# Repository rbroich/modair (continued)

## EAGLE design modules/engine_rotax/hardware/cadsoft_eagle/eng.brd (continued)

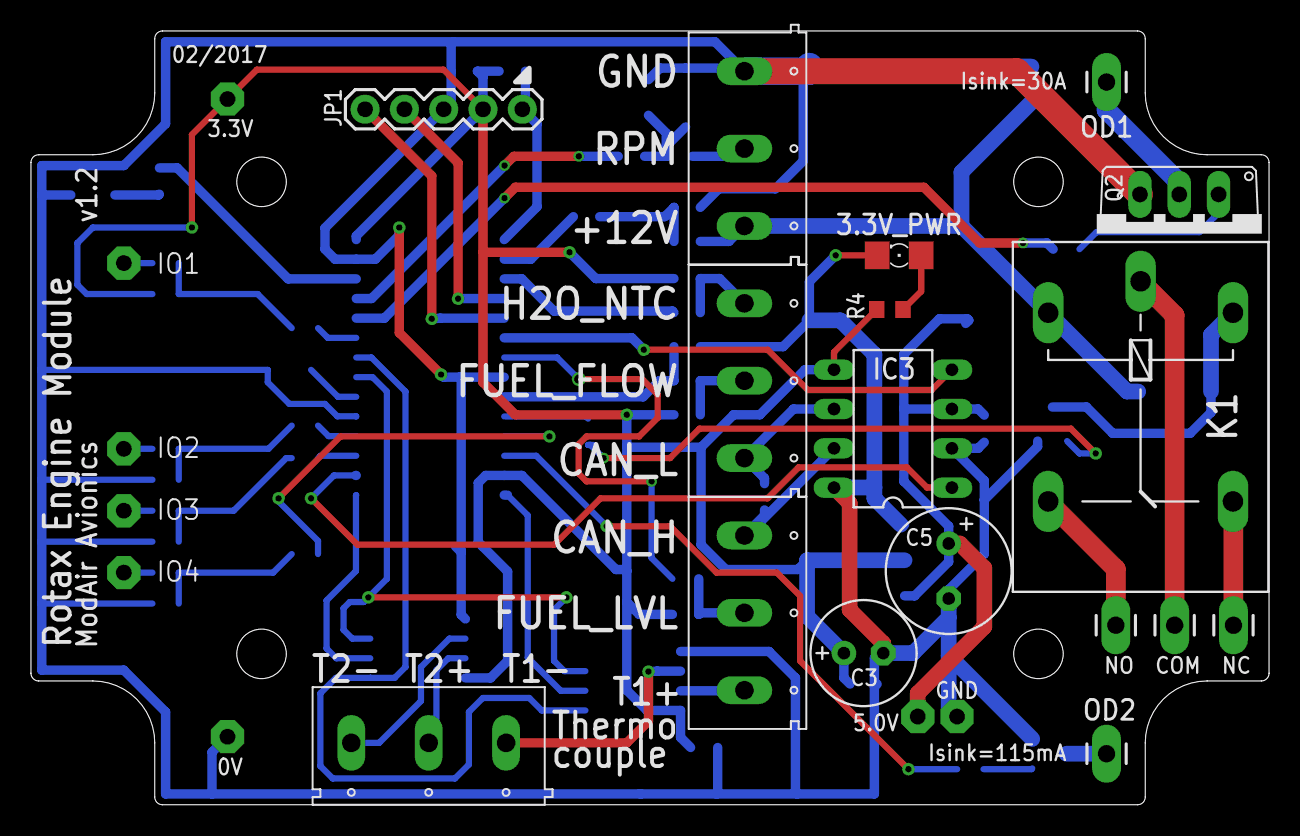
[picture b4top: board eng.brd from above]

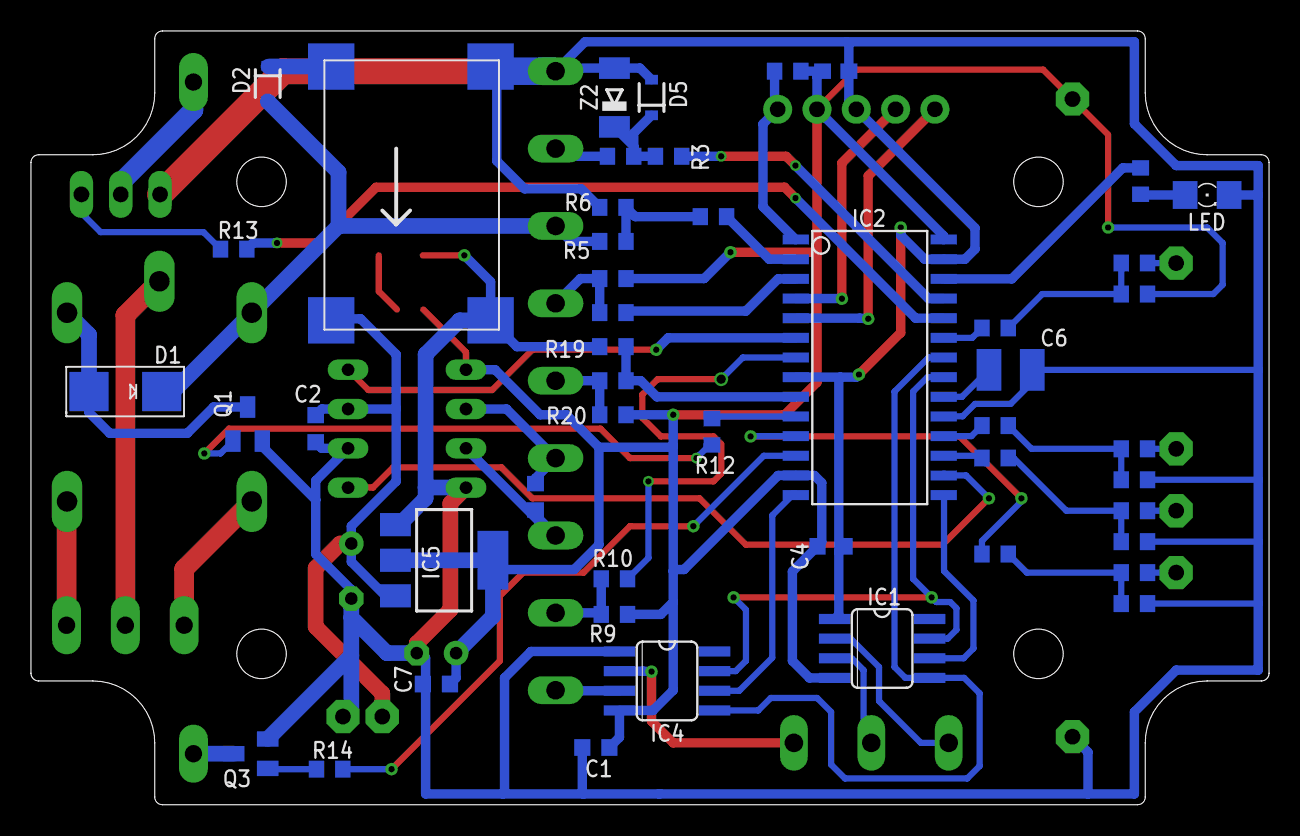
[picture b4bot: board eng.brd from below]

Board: 2 copper layers, 80.0 x 50.0 mm, 73 parts (48 on the bottom side), 59 nets.

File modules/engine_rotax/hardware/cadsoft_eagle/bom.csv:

"Qty";"Value";"Device";"Package";"Parts";"Description";"MF";"MPN";"OC_FARNELL";"OC_NEWARK";"PROD_ID";"VALUE";
"1";"";"DIODESMA";"SMADIODE";"D1";"Diode";"";"";"";"";"";"";
"2";"";"LED-FKIT-1206";"FKIT-LED-1206";"3.3V_PWR, LED";"LEDs";"";"";"";"";"";"";
"5";"";"M01PTH_LONGPAD";"1X01_LONGPAD";"COM, NC, NO, OD1, OD2";"Header 1";"";"";"";"";"";"";
"1";"";"M05PTH";"1X05";"JP1";"Header 5";"";"";"";"";"";"";
"1";"";"MOSFET-NREFLOW";"SOT23";"Q1";"N-Channel Mosfet";"";"";"";"";"";"";
"1";"1000u";"CPOL-EUE3.5-8";"E3,5-8";"C5";"POLARIZED CAPACITOR, European symbol";"";"";"";"";"";"";
"1";"100k";"R-EU_R0603";"R0603";"R18";"RESISTOR, European symbol";"";"";"";"";"";"";
"2";"100n";"C-EUC0603K";"C0603K";"C4, C7";"CAPACITOR, European symbol";"";"";"";"";"";"";
"1";"100u";"CPOL-EUE2.5-7";"E2,5-7";"C3";"POLARIZED CAPACITOR, European symbol";"";"";"";"";"";"";
"1";"10k";"R-EU_R0603";"R0603";"R11";"RESISTOR, European symbol";"";"";"";"";"";"";
"1";"10u";"C-EUC3225";"C3225";"C6";"CAPACITOR, European symbol";"";"";"";"";"";"";
"2";"120";"R-EU_R0603";"R0603";"R9, R21";"RESISTOR, European symbol";"";"";"";"";"";"";
"2";"150";"R-EU_R0603";"R0603";"R1, R4";"RESISTOR, European symbol";"";"";"";"";"";"";
"8";"1k";"R-EU_R0603";"R0603";"R3, R7, R8, R10, R12, R13, R14, R17";"RESISTOR, European symbol";"";"";"";"";"";"";
"1";"1k5";"R-EU_R0603";"R0603";"R6";"RESISTOR, European symbol";"";"";"";"";"";"";
"1";"1u";"C-EUC0603";"C0603";"C9";"CAPACITOR, European symbol";"";"";"";"";"";"";
"2";"1u";"C-EUC0603K";"C0603K";"C1, C2";"CAPACITOR, European symbol";"";"";"";"";"";"";
"1";"200k";"R-EU_R0603";"R0603";"R19";"RESISTOR, European symbol";"";"";"";"";"";"";
"2";"22k";"R-EU_R0603";"R0603";"R2, R5";"RESISTOR, European symbol";"";"";"";"";"";"";
"1";"2n7002";"MOSFET-NREFLOW";"SOT23";"Q3";"N-Channel Mosfet";"";"";"";"";"";"";
"1";"AMS1117-3.3";"LD117AS33TR";"SOT223";"IC5";"Low drop fixed and adjustable positive voltage regulators 1 A";"";"";"";"";"";"";
"1";"DSPIC33EP32GP502-I/SO";"DSPIC33EP32GP502-I/SO";"SO28W";"IC2";"16-Bit Microcontrollers and Digital Signal Controllers";"";"";"";"";"";"";
"1";"IRF540N";"MOSFET-NGDS_TO220V";"TO220V";"Q2";"N-Channel Mosfet";"";"";"";"";"";"";
"1";"JQC-3FF-12";"G5L";"G5LE";"K1";"RELAY";"";"";"unknown";"unknown";"";"";
"8";"LSP10";"LSP10";"LSP10";"0V, 3.3V, 5.0V, GND, IO1, IO2, IO3, IO4";"SOLDER PAD drill 1.0 mm, distributor Buerklin, 12H555";"";"";"";"";"";"";
"2";"MAX6675";"MAX6675";"SO08";"IC1, IC4";"Cold-Junction-Compensated K-Thermocouple-to-Digital Converter";"";"";"";"";"";"";
"1";"MCP2562-E/P";"MCP2562-E/P";"DIL8";"IC3";"High-Speed CAN Transceiver";"";"";"";"";"";"";
"1";"MINI_DC_DC_CONVSMD";"MINI_DC_DC_CONVSMD";"DSN-MINI-360-SMD";"U$1";"RC Airplane Module Mini 360 DC Buck Converter Step Down Module 4.75V-23V to 1V-17V 17x11x3.8mm New LM2596;";"";"";"";"";"";"";
"13";"N/A";"R-EU_R0603";"R0603";"R15, R16, R20, R23, R24, R25, R26, R29, R30, R31, R32, R35, R36";"RESISTOR, European symbol";"";"";"";"";"";"";
"2";"PMEG4005EJ";"DIODE-SCHOTTKY-PMEG4005EJ";"SOD-323";"D2, D5";"Schottky diodes in SFE's production catalog";"";"";"";"";"DIO-10955";"PMEG4005EJ";
"4";"XY301V-A";"XY301V-A";"XY301V-A";"CN1, CN2, CN3, CN4";"3 Pin Screw Terminal Block Connector 5mm Pitch 5.08-301-3P 301-3P 3pin";"";"";"";"";"";"";
"1";"Zener 3.3V";"DIODE-ZENERMM";"MINIMELF";"Z2";"Zener Diode";"";"";"";"";"";"";

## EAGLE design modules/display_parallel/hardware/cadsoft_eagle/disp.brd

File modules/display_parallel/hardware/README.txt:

Different Configurations:

Option 1: 5.8" WITSCHI_ERM25664AAG-1 EastRising 256x64 pixel graphic LCD module Blue backlight.
-LCD goes on top of PCB
-Headers row on the left aligns
-Mounting holes on the left align
-Top right mounting hole aligns with frame ground pad on LCD (solder spacer?)
-Electrolytic Caps C4 and C5 can be bent over
-Contrast Potentiometer not needed (already on LCD module)
-Rot Encoder header attached to Bottom
-LED (or header?) soldered on Bottom
-Screw Terminals attached to Bottom

Option 2: 2.9" NelyTech NT-G128641A 128x64 Graphic LCD Display Module 2xKS0108 Black on White.
-LCD goes on top of PCB
-Headers row on the bottom aligns
-All mounting holes align
-Bend electrolytic caps C4 and C5 over
-Contrast Potentiometer soldered
-Rot Encoder header attached to Bottom
-LED (or header?) soldered on Bottom
-Screw Terminals attached to Bottom

Option 3: 3.1" Generic 5V 12864B V2.0 LCD Display Module 128x64 Dots Graphic Matrix LCD Blue Backlight
-Identical mounting to Option 2
-CS1 becomes PSB [parallel mode] (ST7920, 2MHz clock rate)
-CS2 is not used
-Contrast Potentiometer not needed (already on LCD module)
-Backlight Resistor already on LCD module. Drive with 5V

Option 4: Generic HD44780 2x16 Character LCD Blue Backlight
-Cut PCB Smaller
-LCD goes on top of PCB, rotated 180 degrees
-Headers row on the bottom right aligns
-All mounting holes align
-Rot Encoder mounts vertically on top left PCB (isolate exposed header pins underneath...gnd plate on bottom of rotenc)
-LED mounts vertically on top right
-Electrolytic caps C4 and C5 mount vertically
-Screw Terminals attached to Bottom

ASSEMBLY:
Option 2 & 3:
-3D printed mounting hole standoffs with outer rectangle
-11mm Standoffs (distance between LCD and PCB)
-Male headers on LCD
-Female headers on PCB
-1.6mm PCBs

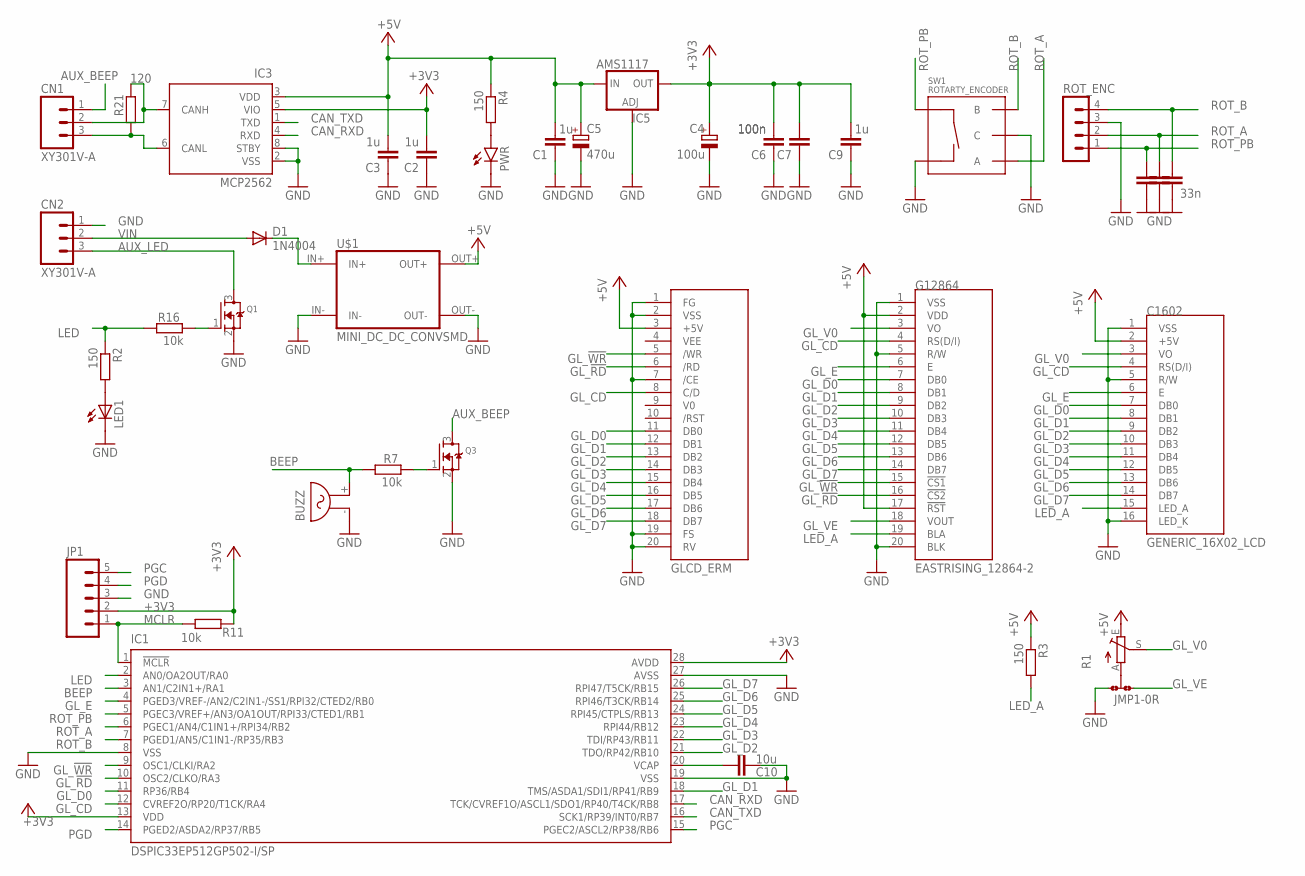
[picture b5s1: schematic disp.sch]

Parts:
BUZZ: F/QMX
C1, C2, C3, C9: 1u; C0603K
C4: 100u; E2,5-7
C5: 470u; E3,5-8
C6, C7: 100n; C0603K
C10: 10u; C025-030X050
C11, C12, C13: 33n; C0603K
C1602: GENERIC_16X02_LCD; 1X16
CN1, CN2: XY301V-A
D1: 1N4004; DO41-10
G12864: EASTRISING_12864-2; 1X20
GLCD_ERM: WITSCHI_ERM25664AAG-1; 1X20
IC1: DSPIC33EP512GP502-I/SP; DIL28-3
IC3: MCP2562; DIL8
IC5: AMS1117; SOT223
JMP1: 0R-JUMPB; B0R-JMP
JP1: M05PTH; 1X05
LED1: LED5MM
PWR: LED-FKIT-1206; FKIT-LED-1206
Q1, Q3: MOSFET-NREFLOW; SOT23
R1: TRIM_EU-B64Y; B64Y
R2, R3, R4: 150; R0603
R7, R11, R16: 10k; R0603
R21: 120; R0603
ROT_ENC: MA04-1
SW1: ROTARTY_ENCODER; ROTARY_ENC_PLAIN
U$1: MINI_DC_DC_CONVSMD; DSN-MINI-360-SMD

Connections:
+3V3: C2.2, C4.+, C6.2, C7.2, C9.2, IC1.13 (VDD), IC1.28 (AVDD), IC3.5 (VIO), IC5.2 (OUT), IC5.@2 (OUT), JP1.2, R11.1
+5V: C1.2, C3.2, C5.+, C1602.2 (+5V), G12864.2 (VDD), G12864.17 (!RST), GLCD_ERM.3 (+5V), IC3.3 (VDD), IC5.3 (IN), R1.E, R3.1, R4.1, U$1.OUT+
AUX_BEEP: CN1.1, Q3.3 (D)
AUX_LED: CN2.3, Q1.3 (D)
BEEP: BUZZ.+ (2), IC1.3 (AN1/C2IN1+/RA1), R7.2
CAN_H: CN1.2, IC3.7 (CANH), R21.2
CAN_L: CN1.3, IC3.6 (CANL), R21.1
CAN_RXD: IC1.17 (TCK/CVREF1O/ASCL1/SDO1/RP40/T4CK/RB8), IC3.4 (RXD)
CAN_TXD: IC1.16 (SCK1/RP39/INT0/RB7), IC3.1 (TXD)
GL_!RD: G12864.16 (!CS2), GLCD_ERM.6 (/RD), IC1.10 (OSC2/CLKO/RA3)
GL_!WR: G12864.15 (!CS1), GLCD_ERM.5 (/WR), IC1.9 (OSC1/CLKI/RA2)
GL_CD: C1602.4 (RS(D/I)), G12864.4 (RS(D/I)), GLCD_ERM.8 (C/D), IC1.12 (CVREF2O/RP20/T1CK/RA4)
GL_D0: C1602.7 (DB0), G12864.7 (DB0), GLCD_ERM.11 (DB0), IC1.11 (RP36/RB4)
GL_D1: C1602.8 (DB1), G12864.8 (DB1), GLCD_ERM.12 (DB1), IC1.18 (TMS/ASDA1/SDI1/RP41/RB9)
GL_D2: C1602.9 (DB2), G12864.9 (DB2), GLCD_ERM.13 (DB2), IC1.21 (TDO/RP42/RB10)
GL_D3: C1602.10 (DB3), G12864.10 (DB3), GLCD_ERM.14 (DB3), IC1.22 (TDI/RP43/RB11)
GL_D4: C1602.11 (DB4), G12864.11 (DB4), GLCD_ERM.15 (DB4), IC1.23 (RPI44/RB12)
GL_D5: C1602.12 (DB5), G12864.12 (DB5), GLCD_ERM.16 (DB5), IC1.24 (RPI45/CTPLS/RB13)
GL_D6: C1602.13 (DB6), G12864.13 (DB6), GLCD_ERM.17 (DB6), IC1.25 (RPI46/T3CK/RB14)
GL_D7: C1602.14 (DB7), G12864.14 (DB7), GLCD_ERM.18 (DB7), IC1.26 (RPI47/T5CK/RB15)
GL_E: C1602.6 (E), G12864.6 (E), IC1.4 (PGED3/VREF-/AN2/C2IN1-/SS1/RPI32/CTED2/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)
GL_V0: C1602.3 (VO), G12864.3 (VO), R1.S
GL_VE: G12864.18 (VOUT), JMP1.3
GND: BUZZ.- (1), C1.1, C2.1, C3.1, C4.-, C5.-, C6.1, C7.1, C9.1, C10.1, C11.1, C12.1, C13.1, C1602.1 (VSS), C1602.5 (R/W), C1602.16 (LED_K), CN2.1, G12864.1 (VSS), G12864.5 (R/W), G12864.20 (BLK), GLCD_ERM.1 (FG), GLCD_ERM.2 (VSS), GLCD_ERM.7 (/CE), GLCD_ERM.19 (FS), GLCD_ERM.20 (RV), IC1.8 (VSS), IC1.19 (VSS), IC1.27 (AVSS), IC3.2 (VSS), IC3.8 (STBY), IC5.1 (ADJ), JMP1.1, JP1.3, LED1.K (C), PWR.C, Q1.2 (S), Q3.2 (S), ROT_ENC.3, SW1.C, SW1.SW-, U$1.IN-, U$1.OUT-
LED: IC1.2 (AN0/OA2OUT/RA0), R2.1, R16.2
LED_A: C1602.15 (LED_A), G12864.19 (BLA), R3.2
MCLR: IC1.1 (!MCLR!), JP1.1, R11.2
unnamed: Q3.1 (G), R7.1
unnamed: LED1.A, R2.2
unnamed: PWR.A, R4.2
unnamed: JMP1.2, R1.A
unnamed: Q1.1 (G), R16.1
PGC: IC1.15 (PGEC2/ASCL2/RP38/RB6), JP1.5
PGD: IC1.14 (PGED2/ASDA2/RP37/RB5), JP1.4
ROT_A: C12.2, IC1.6 (PGEC1/AN4/C1IN1+/RPI34/RB2), ROT_ENC.2, SW1.A
ROT_B: C13.2, IC1.7 (PGED1/AN5/C1IN1-/RP35/RB3), ROT_ENC.4, SW1.B
ROT_PB: C11.2, IC1.5 (PGEC3/VREF+/AN3/OA1OUT/RPI33/CTED1/RB1), ROT_ENC.1, SW1.SW+
V0: GLCD_ERM.9 (V0)
VCAP: C10.2, IC1.20 (VCAP)
VEE: GLCD_ERM.4 (VEE)
VIN: CN2.2, D1.A
VIN_D: D1.C, U$1.IN+

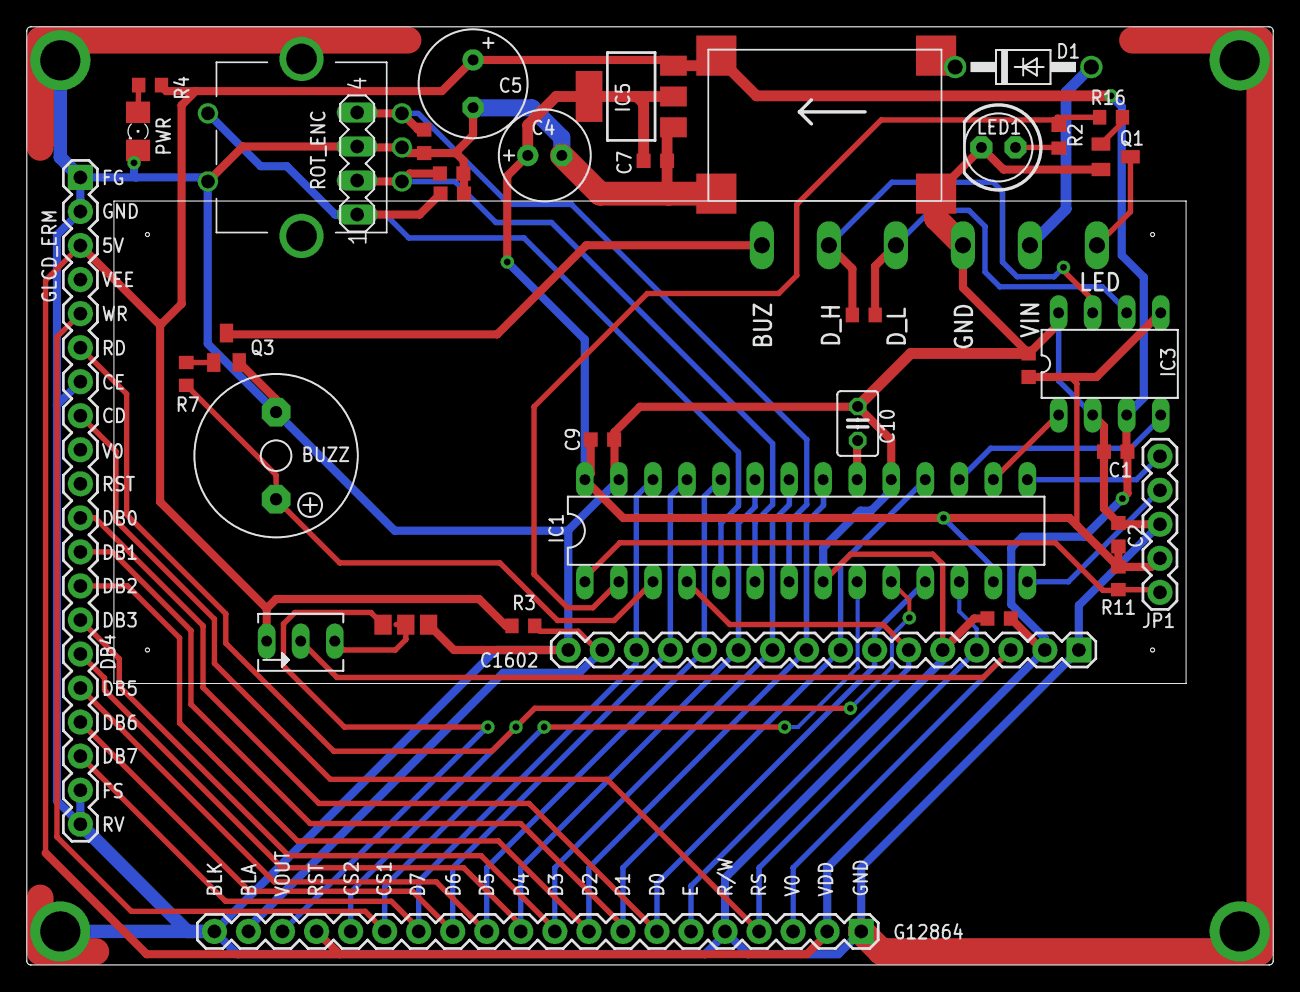
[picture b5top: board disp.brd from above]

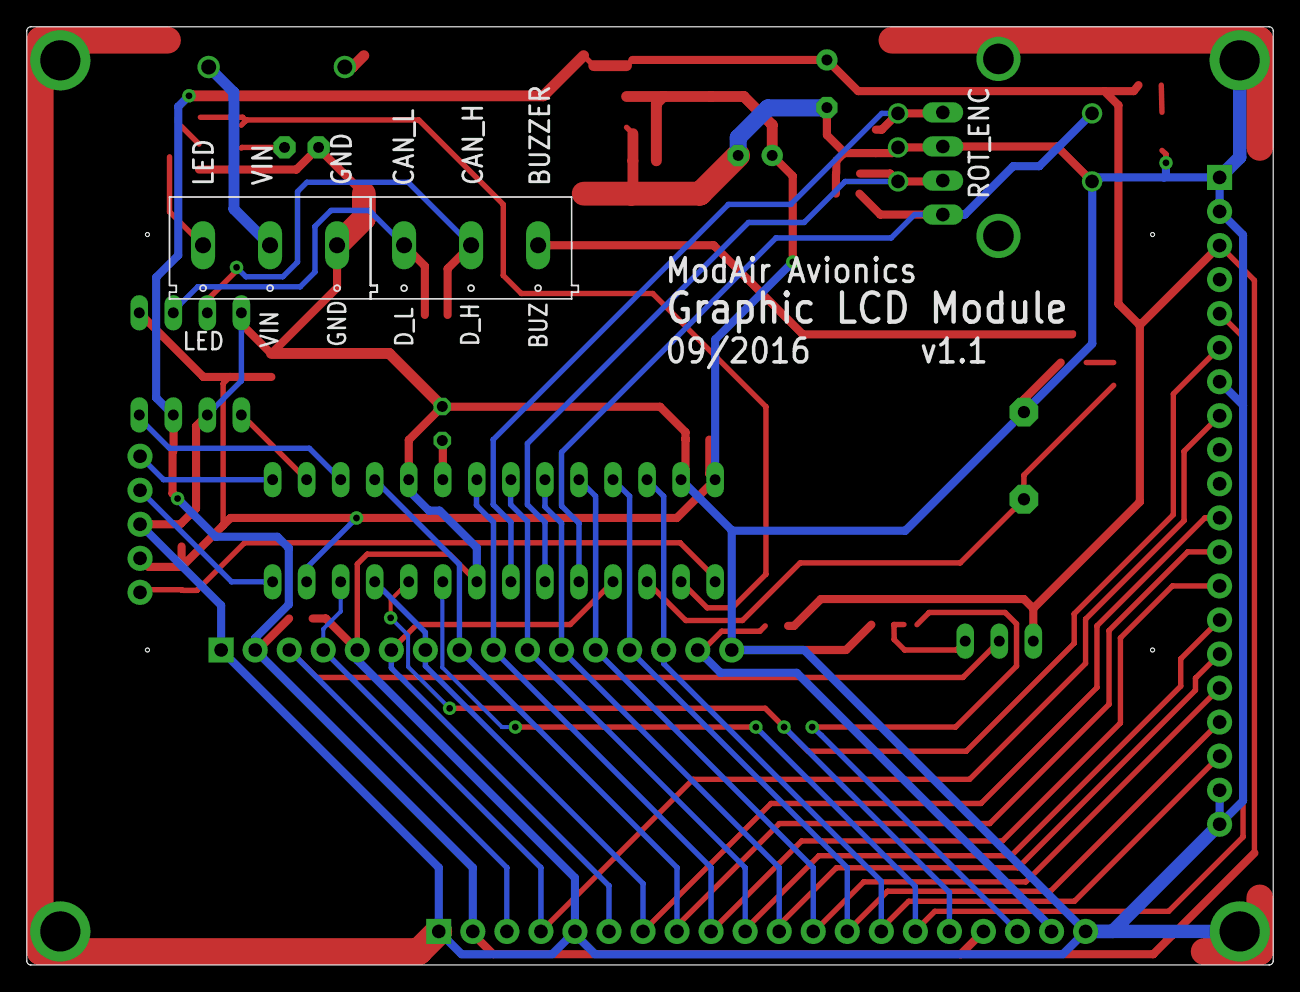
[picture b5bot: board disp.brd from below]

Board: 2 copper layers, 93.0 x 70.0 mm, 39 parts (2 on the bottom side), 40 nets.

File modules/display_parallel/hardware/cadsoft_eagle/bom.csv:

"Qty";"Value";"Device";"Package";"Parts";"Description";"MF";"MPN";"OC_FARNELL";"OC_NEWARK";
"1";"";"LED-FKIT-1206";"FKIT-LED-1206";"PWR";"LEDs";"";"";"";"";
"1";"";"LED5MM";"LED5MM";"LED1";"LED";"";"";"";"";
"1";"";"M05PTH";"1X05";"JP1";"Header 5";"";"";"";"";
"1";"";"MA04-1";"MA04-1";"ROT_ENC";"PIN HEADER";"";"";"unknown";"unknown";
"2";"";"MOSFET-NREFLOW";"SOT23";"Q1, Q3";"N-Channel Mosfet";"";"";"";"";
"1";"";"TRIM_EU-B64Y";"B64Y";"R1";"POTENTIOMETER";"";"";"";"";
"1";"0R-JUMPB";"0R-JUMPB";"B0R-JMP";"JMP1";"SMD 0R 0805 Jumper";"";"";"";"";
"2";"100n";"C-EUC0603K";"C0603K";"C6, C7";"CAPACITOR, European symbol";"";"";"";"";
"1";"100u";"CPOL-EUE2.5-7";"E2,5-7";"C4";"POLARIZED CAPACITOR, European symbol";"";"";"";"";
"3";"10k";"R-EU_R0603";"R0603";"R7, R11, R16";"RESISTOR, European symbol";"";"";"";"";
"1";"10u";"C-EU025-030X050";"C025-030X050";"C10";"CAPACITOR, European symbol";"";"";"";"";
"1";"120";"R-EU_R0603";"R0603";"R21";"RESISTOR, European symbol";"";"";"";"";
"3";"150";"R-EU_R0603";"R0603";"R2, R3, R4";"RESISTOR, European symbol";"";"";"";"";
"1";"1N4004";"1N4004";"DO41-10";"D1";"DIODE";"";"";"";"";
"4";"1u";"C-EUC0603K";"C0603K";"C1, C2, C3, C9";"CAPACITOR, European symbol";"";"";"";"";
"3";"33n";"C-EUC0603K";"C0603K";"C11, C12, C13";"CAPACITOR, European symbol";"";"";"";"";
"1";"470u";"CPOL-EUE3.5-8";"E3,5-8";"C5";"POLARIZED CAPACITOR, European symbol";"";"";"";"";
"1";"AMS1117";"LD117AS33TR";"SOT223";"IC5";"Low drop fixed and adjustable positive voltage regulators 1 A";"";"";"";"";
"1";"DSPIC33EP512GP502-I/SP";"DSPIC33EP512GP502-I/SP";"DIL28-3";"IC1";"16-Bit Microcontrollers and Digital Signal Controllers";"";"";"";"";
"1";"EASTRISING_12864-2";"EASTRISING_12864-2";"1X20";"G12864";"2.9"128x64 Graphic LCD Display Module KS0108 Black on White.";"";"";"";"";
"1";"F/QMX";"F/QMX";"F/QMX";"BUZZ";"BUZZER Source: Buerklin";"";"";"unknown";"unknown";
"1";"GENERIC_16X02_LCD";"GENERIC_16X02_LCD";"1X16";"C1602";"";"";"";"";"";
"1";"MCP2562";"MCP2562-E/P";"DIL8";"IC3";"High-Speed CAN Transceiver";"";"";"";"";
"1";"MINI_DC_DC_CONVSMD";"MINI_DC_DC_CONVSMD";"DSN-MINI-360-SMD";"U$1";"RC Airplane Module Mini 360 DC Buck Converter Step Down Module 4.75V-23V to 1V-17V 17x11x3.8mm New LM2596;";"";"";"";"";
"1";"ROTARTY_ENCODER";"ROTARTY_ENCODER";"ROTARY_ENC_PLAIN";"SW1";"Simple no LED rotary encoder";"";"";"";"";
"1";"WITSCHI_ERM25664AAG-1";"WITSCHI_ERM25664AAG-1";"1X20";"GLCD_ERM";"EastRising 256x64 pixel graphic LCD module";"";"";"";"";
"2";"XY301V-A";"XY301V-A";"XY301V-A";"CN1, CN2";"3 Pin Screw Terminal Block Connector 5mm Pitch 5.08-301-3P 301-3P 3pin";"";"";"";"";

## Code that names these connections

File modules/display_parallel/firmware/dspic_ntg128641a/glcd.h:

#ifndef GLCD_H
#define GLCD_H

// 2.9" NelyTech NT-G128641A 128x64 Graphic LCD Display Module, Black on White
// PCB 93x70 mm
// 2 x KS0108 Controllers

// All minimum timing requirements multiplied by 2 (fosc 270kHz instead of 540kHz)

// Pin 01 VSS
// Pin 02 VDD
// Pin 03 V0
// Pin 04 RS (RS=H:data  RS=L:instruction)
// Pin 05 R/W (RW=H:read  RW=L:write)
// Pin 06 E
// Pin 07 DB0
// Pin ......
// Pin 14 DB7
// Pin 15 CS1
// Pin 16 CS2
// Pin 17 /RST
// Pin 18 VOUT
// Pin 19 LED A (+)
// Pin 20 LED K (-)

// Standard graphical axis
// x=0: left
// x=LCD_X-1: right
// y=0: top
// y=LCD_Y-1: bottom

#include "common.h"

#define ROTATE_SCREEN_90        1
#if ROTATE_SCREEN_90
  #define LCD_X                   64
  #define LCD_Y                   128
#else
  #define LCD_X                   128
  #define LCD_Y                   64
#endif
#define LCD_WHITE               0
#define LCD_BLACK               1

#define GL_RS_INSTR             0
#define GL_RS_DATA              1

#define GL_RS                   _LATA4 // GL_CD
#define GL_E                    _LATB0
#define GL_D0                   _LATB4
#define GL_D1                   _LATB9
#define GL_D2                   _LATB10
#define GL_D3                   _LATB11
#define GL_D4                   _LATB12
#define GL_D5                   _LATB13
#define GL_D6                   _LATB14
#define GL_D7                   _LATB15
#define GL_CS1                  _LATA2 // GL_CS1 == GL_!WR
#define GL_CS2                  _LATA3 // GL_CS2 == GL_!RD

#define LCD_SET_ADDR            0x40
#define LCD_SET_PAGE            0xB8
#define LCD_START_LINE          0xC0
#define LCD_OFF                 0x3E
#define LCD_ON                  0x3F

#define lcd_ctrl_out()  (TRISA &= 0b1111111111100011)
#define lcd_dir_out()   (TRISB &= 0b0000000111101110)
#define lcd_data_out(x) (LATB = (LATB&0b111101111) | ((x&0xFE)<<8) | ((x&0x01)<<4))



void lcd_out(u8 val);
void lcd_cmd(u8 val);
void lcd_init(void);
void lcd_fill(u8 color);
void lcd_update(void);
void lcd_clrbuff(void);
void lcd_setpixel(u8 x, u8 y, u8 color);

#endif

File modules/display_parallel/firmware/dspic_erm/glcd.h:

#ifndef GLCD_H
#define GLCD_H

#include "common.h"

#define LCD_Y           64
#define LCD_X           256
#define LCD_WHITE       0
#define LCD_BLACK       1

#define LCD_CHAR_WIDTH  8 // 6 or 8 bits depending on FS (H:6x8 L:8x8)

#define LCD_D7          _RB15
#define LCD_D6          _RB14
#define LCD_D5          _RB13
#define LCD_D4          _RB12
#define LCD_D3          _RB11
#define LCD_D2          _RB10
#define LCD_D1          _RB9
#define LCD_D0          _RB4
#define LCD_nWE         _LATA2
#define LCD_nRE         _LATA3
#define LCD_CD          _LATA4

#define lcd_out(x)      (LATB = (LATB&0b111101111) | ((x&0xFE)<<8) | ((x&0x01)<<4))
#define lcd_in(x)       (x = ((PORTB&0xFE00) >> 8) | ((PORTB&0x0010)>>4))
#define lcd_dir_in()    (TRISB |= 0b1111111000010000)
#define lcd_dir_out()   (TRISB &= 0b0000000111101111)
#define lcd_ctrl_out()  (TRISA &= 0b1111111111100011)
#define lcd_cd_cmd()    (LCD_CD=1)
#define lcd_cd_data()   (LCD_CD=0)
#define lcd_rw_idle()   {LCD_nWE=1;LCD_nRE=1;}
#define lcd_rw_rd()     {LCD_nWE=1;LCD_nRE=0;}
#define lcd_rw_wr()     {LCD_nWE=0;LCD_nRE=1;}

/* Define the Memory Map */
#define LCD_GRAPHICS_HOME   0x0000  /* This will usually be at the start of RAM */
#define LCD_GRAPHICS_AREA   0x14    /* A graphic character is 8 bits wide (same as 8x8 char) */
#define LCD_GRAPHICS_SIZE   0x0800  /* Size of graphics RAM */
#define LCD_TEXT_HOME       0x0A00  /* Graphics Area + Text Attribute Size (same size as text size) */
#define LCD_TEXT_AREA       0x14    /* Text line is 20 chars wide */
#define LCD_TEXT_SIZE       0x0200  /* Size of text RAM */

// Control Words
#define LCD_CURSOR_POINTER_SET          0b00100001
#define LCD_OFFSET_REGISTER_SET         0b00100010
#define LCD_ADDRESS_POINTER_SET         0b00100100
#define LCD_TEXT_HOME_ADDRESS_SET       0b01000000
#define LCD_TEXT_AREA_SET               0b01000001
#define LCD_GRAPHIC_HOME_ADDRESS_SET    0b01000010
#define LCD_GRAPHIC_AREA_SET            0b01000011

#define LCD_CG_ROM_MODE_OR              0b10000000
#define LCD_CG_ROM_MODE_EXOR            0b10000001
#define LCD_CG_ROM_MODE_AND             0b10000011
#define LCD_CG_ROM_MODE_TEXT            0b10000100
#define LCD_CG_RAM_MODE_OR              0b10001000
#define LCD_CG_RAM_MODE_EXOR            0b10001001
#define LCD_CG_RAM_MODE_AND             0b10001011
#define LCD_CG_RAM_MODE_TEXT            0b10001100

// OR together for ON modes
#define LCD_DISPLAY_MODES_ALL_OFF       0b10010000
#define LCD_DISPLAY_MODES_GRAPHICS_ON   0b10011000
#define LCD_DISPLAY_MODES_TEXT_ON       0b10010100
#define LCD_DISPLAY_MODES_CURSOR_ON     0b10010010
#define LCD_DISPLAY_MODES_CURSOR_BLINK  0b10010001

// Cursor Pattern Select
#define LCD_CURSOR_PATTERN_UNDERLINE    0b10100000
#define LCD_CURSOR_PATTERN_BLOCK        0b10100111

// Send Auto_XX Command, then block of data, then Auto_reset
#define LCD_DATA_AUTO_WRITE_SET         0b10110000
#define LCD_DATA_AUTO_READ_SET          0b10110001
#define LCD_DATA_AUTO_RESET             0b10110010

// Send R/W Then one byte Data
#define LCD_DATA_WRITE_AUTO_INCREMENT   0b11000000
#define LCD_DATA_READ_AUTO_INCREMENT    0b11000001
#define LCD_DATA_WRITE_NO_INCREMENT     0b11000100
#define LCD_DATA_READ_NO_INCREMENT      0b11000101

// Status Register Bits
#define LCD_STATUS_BUSY1    0x01
#define LCD_STATUS_BUSY2    0x02
#define LCD_STATUS_DARRDY   0x04
#define LCD_STATUS_DAWRDY   0x08
#define LCD_STATUS_CLR      0x20
#define LCD_STATUS_ERR      0x40
#define LCD_STATUS_BLINK    0x80

void lcd_write_command(u8 cmd);
void lcd_write_data(u8 data);
u8 lcd_read_data(void);
u8 lcd_read_status(void);
void lcd_init(void);
void lcd_update(void);
void lcd_clrbuff(void);
void lcd_setpixel(u8 x, u8 y, u8 color);

#endif

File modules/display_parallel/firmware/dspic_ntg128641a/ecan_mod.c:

#include "ecan_mod.h"

__attribute__((aligned(NR_ECAN_BUF*16))) u16 ecan_buf[NR_ECAN_BUF][8];

extern void ecan_rx(u16 pid, u16 *data, u8 msg_type, u8 flags, u8 len);

void ecan_irq(void)
{
    u8 buf_sel = C1VECbits.ICODE;
    if (!(ecan_buf[buf_sel][0] & 0x0001)) // Extended Identifier (29-bit ID)
        return;

    // CID = CAN-ID = 0b000s.ssss.ssss.ssee.eeee.eeee.eeee.eeee
    // where s [bit28:18] = SID (11 bit)
    //       e [bit17:00] = EID (18 bit)
    u8 msg_type = (ecan_buf[buf_sel][0] & 0x0FF0) >> 4;
    u8 len = ecan_buf[buf_sel][2]&0x000F; // Data Length Code
    u16 pid = ecan_buf[buf_sel][2] >> 10;
    pid |= ecan_buf[buf_sel][1] << 6;
    u8 flags = (ecan_buf[buf_sel][1] & 0x0C00) >> 10;
    if (ecan_buf[buf_sel][2] & 0x0200) // remote frame request
        flags |= ECAN_FLAGS_RTR;
    ecan_rx(pid, &ecan_buf[buf_sel][3], msg_type, flags, len);
    C1RXFUL1 = 0xFFFF ^ (1<<buf_sel); // Clear Rx Buffer Full Flag
    C1INTFbits.TBIF = 0; // Clear TX Buffer Interrupt Flag
    C1INTFbits.RBIF = 0; // Clear RX Buffer Interrupt Flag
}

void ecan_tx(u16 pid, u16 d0, u16 d2, u16 d4, u16 d6, u8 msg_type, u8 flags, u8 len)
{
    while (_TXREQ0) ; // wait for first transmit buffer to become available
    // Always transmit using Extended Identifier format
    ecan_buf[0][0] = (msg_type<<4) | 0b11;
    ecan_buf[0][1] = ((pid&0xFFC0)>>6) | ((flags&0x03)<<10);
    ecan_buf[0][2] = ((pid&0x003F)<<10) | ((flags&ECAN_FLAGS_RTR)?0x200:0) | len;
    ecan_buf[0][3] = d0; // byte 0 and 1
    ecan_buf[0][4] = d2; // byte 2 and 3
    ecan_buf[0][5] = d4; // byte 4 and 5
    ecan_buf[0][6] = d6; // byte 6 and 7
    _TXREQ0=1;
}

void ecan_init(void)
{
    // I/O Pin direction, mode, and re-mapping (PPS)
    U1RXt = INPUT_PIN;
    U1TX = 1; // recessive state by default
    U1TXt = OUTPUT_PIN;
    U1RXa = DIGITAL_PIN;
    _RP39R = 14; // CAN_TXD (output) RB7 == RP39 <- C1TX (TABLE 11-3 in DS70000657H)
    _C1RXR = 40; // CAN_RXD (input)  RB8 == RP40 -> C1RX (TABLE 11-2 in DS70000657H)

    C1CTRL1bits.REQOP = 0b100; // enter config mode
    while(C1CTRL1bits.OPMODE != 0b100); // wait for config mode

    // Memory Map Select (0 or 1: C1CTRLx,C1VEC,C1FCTRL,C1FIFO,C1INTF,C1INTE,C1EC,C1CFGx,C1FEN1,C1FMSKSELx)

    // Set Bit Timing to 1 Mbps
    // N = 20 time quanta per bit;   FTQ = N x baud = 20 MHz
    C1CTRL1bits.CANCKS = 1; // FCAN is equal to 2*FP (==2*F_CY)
    C1CFG2bits.SEG1PH = 0x7; // Phase Segment 1 time is 8 TQ
    C1CFG2bits.SEG2PHTS = 0x1; // Phase Segment 2 time is set to be programmable
    C1CFG2bits.SEG2PH = 0x5; // Phase Segment 2 time is 6 TQ
    C1CFG2bits.PRSEG = 0x4; // Propagation Segment time is 5 TQ
    C1CFG2bits.SAM = 0x1; // Bus line is sampled three times at the sample point
    C1CFG1bits.SJW = 0x3; // Synchronization Jump Width set to 4 TQ
    C1CFG1bits.BRP = 0x2; // Baud Rate Prescaler = FCAN /(2*FTQ) -1

    // Memory Map Select (1: C1BUFPNTx,C1RXMxSID,C1RXMxEID,C1RXFxSID,C1RXFxEID)
    C1CTRL1bits.WIN = 1;

    // Configure Receive Buffers [buffers 8 to 15]
    C1FCTRLbits.DMABS = 0b100; // 16 buffers in device RAM
    C1FCTRLbits.FSA = 8; // FIFO starts at buffer 8 (rx buffers)
    C1RXF0SIDbits.SID = 0; // configure filter 0
    C1RXF0SIDbits.EXIDE = 1; // extended identifier address
    C1RXF0SIDbits.EID = 0;
	C1RXF0EIDbits.EID = 0;
    C1BUFPNT1bits.F0BP = 0b1111; // assign filter 0 to FIFO
    C1RXM0SIDbits.SID = 0; // configure mask 0 (all bits are ignored in filter comparison)
    C1RXM0EIDbits.EID = 0;
    C1FMSKSEL1bits.F0MSK = 0; // select mask 0 for filter 0
	C1FEN1 = 0x1; // enable filter 0

    // Memory Map Select (0: C1RXFULx,C1RXOVFx,C1TRxxCON,C1RXD,C1TXD)
    C1CTRL1bits.WIN = 0;

    // Configure Transmit Buffers [buffers 0 to 7]
    C1TR01CONbits.TXEN0 = ENABLE; // buffers are transmit buffers
    C1TR01CONbits.TXEN1 = ENABLE;
    C1TR23CONbits.TXEN2 = ENABLE;
    C1TR23CONbits.TXEN3 = ENABLE;
    C1TR45CONbits.TXEN4 = ENABLE;
    C1TR45CONbits.TXEN5 = ENABLE;
    C1TR67CONbits.TXEN6 = ENABLE;
    C1TR67CONbits.TXEN7 = ENABLE;

    // Setup DMA0 for TX_RAM -> CAN_TX
    DMA0CONbits.SIZE = 0x0; // word instead of byte
    DMA0CONbits.DIR = 0x1; // read from RAM address, write to peripheral address
    DMA0CONbits.AMODE = 0x2; // Peripheral Indirect Addressing mode
    DMA0CONbits.MODE = 0x0; // Continuous, Ping-Pong modes disabled
    DMA0REQ = 70; // DMA Peripheral IRQ Number Select: ECAN1 ? TX Data Request
    DMA0CNT = 7;
    DMA0PAD = (volatile u16)&C1TXD;
    DMA0STAL = (u16)&ecan_buf[0][0];
    DMA0STAH = (u16)&ecan_buf[0][0];
    DMA0CONbits.CHEN = ENABLE;

    // Setup DMA1 for CAN_RX -> RX_RAM
    DMA1CONbits.SIZE = 0x0; // word instead of byte
    DMA1CONbits.DIR = 0x0; // Read from Peripheral address, write to RAM address
    DMA1CONbits.AMODE = 0x2; // Peripheral Indirect Addressing mode
    DMA1CONbits.MODE = 0x0; // Continuous, Ping-Pong modes disabled
    DMA1REQ = 34; // DMA Peripheral IRQ Number Select: ECAN1 ? RX Data Ready
    DMA1CNT = 7;
    DMA1PAD = (volatile u16)&C1RXD;
    DMA1STAL = (u16)&ecan_buf[0][0];
    DMA1STAH = (u16)&ecan_buf[0][0];
    DMA1CONbits.CHEN = ENABLE;

    C1CTRL1bits.REQOP = 0; // enter normal mode
    while(C1CTRL1bits.OPMODE != 0); // wait for normal mode

    C1INTEbits.RBIE = ENABLE; // Receive Buffer Interrupt Enable
}

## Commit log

2017-03-26 First manufacturing batch
    Hardware:
    Parallel Transflective LCD Modules: 16x2, 128x64, 256x64.
    Rotax Engine Interface Module.
    Firmware:
    Initial test code for all components
2017-04-04 Nelytech GLCD Initial Test
    Printed pixels to screen... still need to write efficient buffer copy
    function
2017-04-04 Removed buffer from main, and added it under glcd
2017-04-08 changed rotary encoder input to be compatible with ASCII
    future plan: allow remote menu or keyboard input
2017-04-08 first version of new menu structure using function pointers
2017-04-08 rotated screen by -90 degrees
2017-04-12 added schematic pdf
2017-04-23 Added ModAirBus defines, CAD 3D brackets for LCD mounting
2017-04-23 reverted main branch back to non-rotated lcd
    new branch now has 90 degree rotated version
2017-04-23 First Remote Console implementation.... untested
2017-04-24 proof of concept for remote console on Engine module
2017-04-25 proof of concept remote console working for module menu
2017-04-28 restructured to allow for simpler parameter implementations
2017-04-28 added a bunch of parameters to the engine module
2017-04-29 added menu_fnc_ptr to the PARAM_CONST structure, and handle remote console function calls from main.c... this greatly simplifies parameter.c
2017-04-30 added block diagrams, added engine_rotax RTR response
2017-04-30 fixed readme block diagram link, added hackaday project link
2017-05-07 proof of concept for pod
2017-05-07 pod test...Alt,Hdg,Speed
2017-05-13 pressure sensor interface to gy87 working
2017-05-13 gy87 compass and gyro/acc interfaces working
2017-05-23 RPM bug fix: count only on rising edge rather than on change notification
2017-08-09 added compass and made the NT12864 module widgets look nice
2018-09-27 added UTC time field
2018-09-27 work in progress on the navigation module to fit the Hammond enclosure
2018-09-27 ERC240160 3D printed enclosure (initial FDM version)
2018-10-14 initial FPC LCD hardware with DC-DC converter module
2018-12-29 the RBF flag does not seem to be set anymore; checking only the receiver status seems to work though
2018-12-29 added some of the parameters from the engine module (nav firmware is used for testing using a modified engine module)
2018-12-29 grouped all user-modifiable settings into a single structure, such that the entire memory page can be erased, modified in RAM and re-written to flash.
    having separate settings records makes tracking memory offsets (in both RAM and Flash) more cumbersome
2018-12-29 discrepancy between 16-Bit_Language_Tools_Libraries_Manual.pdf and the flash_helper.s source file:
    _write_flash16 does not seem to work, and _write_flash_word32 works (even though the docs say it's currently disabled)
2018-12-30 completed parameter settings in the module menu
2019-01-03 added calibration menu for fuel_level,
    merged IO pins to single C/H file and added menus.
2019-01-03 added SET_VALUE handler for iopins
2019-01-05 changed Fcy to 50 MIPS to avoid Fclk overlap with VHF radio airband
2019-01-08 added remaining parameters from the engine module
2019-01-13 added code to update logged engine hours to flash memory (untested)
